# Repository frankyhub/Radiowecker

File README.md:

<div align="center">

|[:skull:ISSUE](https://github.com/frankyhub/Radiowecker/issues?q=is%3Aissue)|[:speech_balloon: Forum /Discussion](https://github.com/frankyhub/Radiowecker/discussions)|[:grey_question:WiKi](https://github.com/frankyhub/Radiowecker/wiki)||
|--|--|--|--|
| | | | |
<a href="https://github.com/frankyhub/Radiowecker/issues">|<a href="https://github.com/frankyhub/Radiowecker/discussions">|<a href="https://github.com/frankyhub/Radiowecker/6eleases">||
|| <a href="https://github.com/frankyhub/Radiowecker/pulse" alt="Activity">| <a href="https://github.com/frankyhub/Radiowecker/graphs/traffic">  |<a href="https://github.com/frankyhub?tab=stars"> ||

<br>
  
<br> <br>

</div>

## Story
Das Repo beschreibt einen Radiowecker mit einem 2,8"T FT-Display, einem 3W Klasse D Amplifier und einen WEB-Server. Zwei Weckzeiten können an beliebigen Wochentagen zugeordnet werden. Es ist auch ein Einschlaf-Timer vorhanden. Mit dem LDR kann man die Display-Helligkeit automatisch an die Raumhelligkeit anpassen. Über den Touchscreen sind Radio ein/aus, Einschlaftimer mit Einschlafzeit, Wecker ein/aus, Senderauswahl und Lautstärke einstellbar. Die Weckzeiten und die Stream-URLs der Radiostationen werden über ein Web-Interface konfiguriert.

Nach einer Idee und Vorlage von 

https://www.az-delivery.de/blogs/azdelivery-blog-fur-arduino-und-raspberry-pi/internet-radiowecker-mit-touchscreen.

## Inbetriebnahme

### Verdrahtung 

| TFT-Display | ESP32 | 
| -------- | -------- | 
|  VCC  |  3,3V  |
|  GND |   GDN |
| CS  | GPIO5  |
| RESET  | GPIO22   |
| DC | NC  |
| SDI  | GPIO23    |
| SCK  |  GPIO18  |
|  LED |  GPIO15  |
|  MISO | GPIO19   | 
| T-CLK  | GPIO18 |    
| T-CS  | GPIO14  | 
| T-DIN  | GPIO23  | 
| T-DO  | GPIO19  | 
| T-IRQ  | GPIO27  | 
|  --- |  --- | 

<br> <br>

### ESP32 TFT 2.8" Shield

<br> <br>

### Gehäuse

<br> <br>

### Nach anlegen der Versorgungsspannung startet der Accesspoit. In den Einstellungen des Handys oder Tablets wird das WLAN "Radiowecker" ausgewählt 

<br> <br>

<br> <br>

### und über einen Browser die URL 192.168.4.1 eingegeben und der Neustart-Button betätigt.

<br> <br>

### Am Seriellen Monitor kann der Startvorgang beobachtet und die IP-Adresse des WEB-Servers abgelesen werden.

<br> <br>

### Am Display wird beim Startvorgang die WLAN-Verbindung angezeigt.

<br> <br>

### Nach dem Aufruf des WEB-Server sieht man die Einstellungen und passt diese an.

<br> <br>

### Die Bedienung kann auch über das TFT-Display erfolgen.

<br> <br>

<br> <br>

## Bedienung

### Radio ein/aus
Das Radio wird ein- oder ausgeschaltet. Die Anzeige kehrt zur Zeitanzeige zurück. Wurde das Radio eingeschaltet, erscheint unter der Zeitanzeige der Radioblock mit dem Sendernamen.

### Einschlaftimer
Die Einschlafzeit wird gestartet. Falls das Radio nicht eingeschaltet ist, wird es eingeschaltet. Die Anzeige kehrt zur Zeitanzeige zurück. Wenn die eingestellte Einschlafzeit vorüber ist, wird das Radio automatisch ausgeschaltet.

### Wecker ein/aus
Die Wecker-Funktion wird ein- oder ausgeschaltet. Die Anzeige kehrt zur Zeitanzeige zurück. Wurde der Wecker eingeschaltet, erscheint ganz unten im Display der Wochentag und die Uhrzeit, wann der Wecker das nächste Mal ausgelöst wird. Wenn der angezeigte Wochentag und die Uhrzeit zutreffen, wird das Radio automatisch eingeschaltet.

### Sender speichern
Der ausgewählte Sender wird als aktiver Sender übernommen. Ist das Radio gerade eingeschaltet, so wechselt der Stream automatisch auf den neuen Sender. Die Anzeige kehrt zur Zeitanzeige zurück.

### Zurück
Die Anzeige kehrt zur Zeitanzeige zurück.

Erfolgt 10 Sekunden keine Aktivität, so kehrt die Anzeige automatisch zur Zeitanzeige zurück. Alle Einstellungsänderungen werden in den Präferenzen gespeichert. Die Bedienungsseite wird immer mit voller Helligkeit dargestellt.

<br> <br>

## Konfiguration

### Über die URL http://radiowecker/ sollte die Konfigurationsseite abrufbar sein. 

<br> <br>

Im oberen Teil sieht man die WLAN-Zugangsdaten und den NTP-Server. Mit dem "Speichern-Button" werden Änderungen wirksam. Auch ein Neustart ist möglich. Als Nächstes folgen die Weckzeiten. Zwei Weckzeiten sind möglich. Für jede der Weckzeiten sind die Wochentage wählbar, an denen die Weckzeiten anzuwenden sind. Die Dropdown-Liste darunter enthält alle Sender der Senderliste. Auswählbare Sender haben vor dem Namen einen schwarzen Punkt. Im Formular darunter werden die Daten zur ausgewählten Station angezeigt und können geändert werden. Ist das Häkchen bei „Verwenden“ nicht gesetzt, ist die Station im Gerät nicht aktiv. Da manche URLs nicht funktionieren, sollte man eine neue URL erstmal testen. Ein Klicken auf den "Testen-Button" startet die Wiedergabe der URL am eingeschalteten Gerät. Sollte die Wiedergabe nicht funktionieren, wird wieder auf den aktuellen Sender zurückgeschaltet und eine Meldung angezeigt. Ist die Wiedergabe möglich, wird eine Box mit einem Knopf angezeigt. Klicken auf diesen Knopf schließt die Box und beendet den Test. Es wird wieder die aktuelle Station wiedergegeben. Im Eingabefeld „Position“ wird die Position der ausgewählten Station innerhalb der Senderliste angezeigt. Durch eine Änderung dieses Wertes, kann die Station auf die angegebene Position verschoben und mit dem Knopf „Ändern“ können die Änderungen für die ausgewählte Station dauerhaft geändert werden.

---

<br> <br>

---

<div style="position:absolute; left:2cm; "> <ol class="breadcrumb" style="border-top: 2px solid black;border-bottom:2px solid black; height: 45px; width: 900px;"> <p align="center"><a href="#oben">nach oben</a></p></ol>
</div>  

---

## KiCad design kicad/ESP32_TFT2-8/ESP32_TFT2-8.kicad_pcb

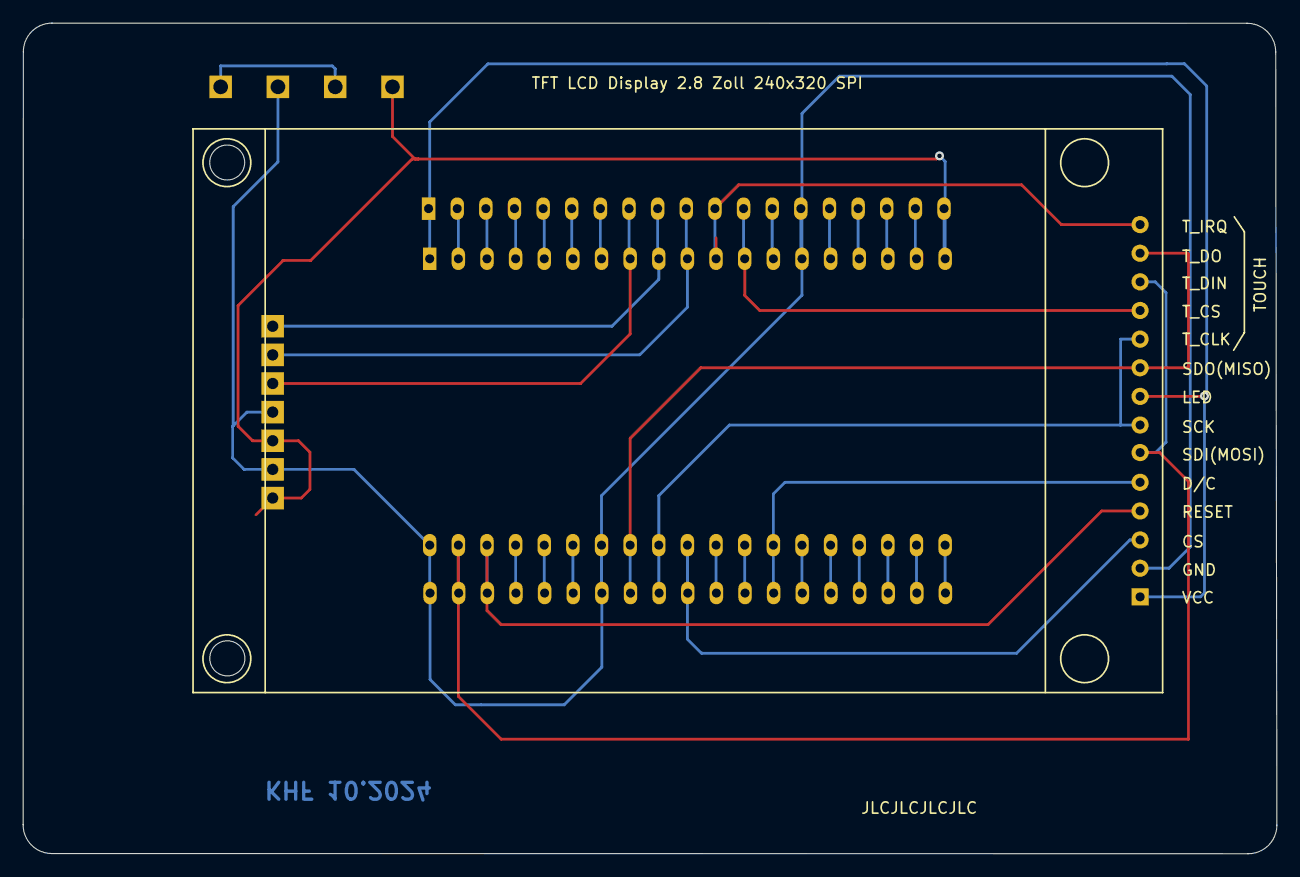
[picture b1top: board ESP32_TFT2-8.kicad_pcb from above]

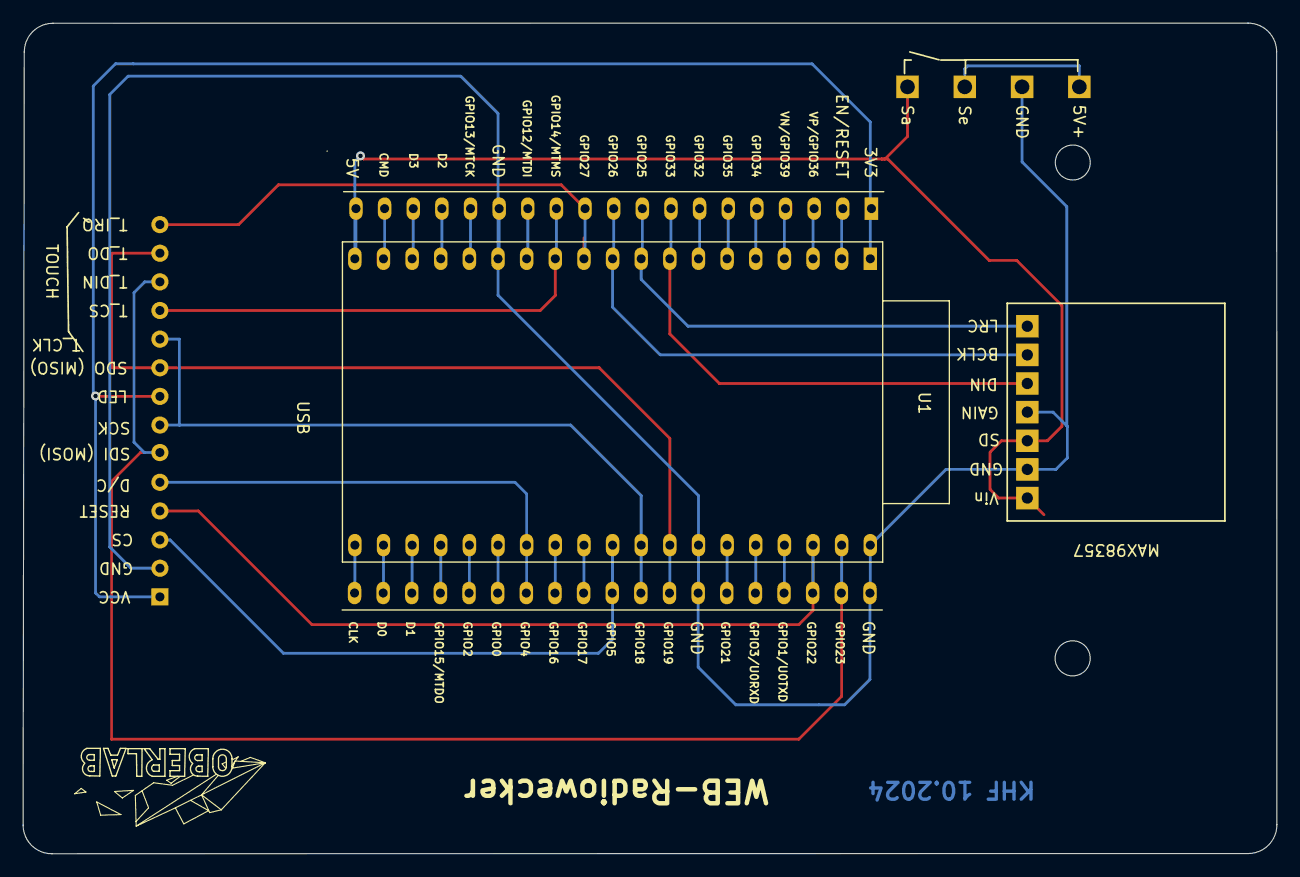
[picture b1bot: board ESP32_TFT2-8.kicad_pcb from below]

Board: 2 copper layers, 111.2 x 73.7 mm, 13 parts (8 on the bottom side), 14 nets.

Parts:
U1: ESP32-DevKitC
U2: 2.8_tft_240x320_touch_sd_spi
U3: 5V+; LP
U4, U8: GND; LP
U5: Se; LP
U6: Sa; LP
U7: Vin; LP
U9: SD; LP
U10: GAIN; LP
U11: DIN; LP
U12: BCLK; LP
U13: LRC; LP

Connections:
unnamed: U1.1 (3V3), U2.1 (VCC), U2.8 (LED)
unnamed: U1.19 (5V), U6.1 (LP), U7.1 (LP), U9.1 (LP)
unnamed: U1.8 (32K_XN/GPIO33/ADC1_CH5), U11.1 (LP)
unnamed: U1.11 (ADC2_CH7/GPIO27), U2.14 (T_IRQ)
unnamed: U1.9 (DAC_1/ADC2_CH8/GPIO25), U13.1 (LP)
unnamed: U1.10 (DAC_2/ADC2_CH9/GPIO26), U12.1 (LP)
unnamed: U1.29 (GPIO5), U2.3 (CS)
unnamed: U1.30 (GPIO18), U2.7 (SCK), U2.10 (T_CLK)
unnamed: U1.31 (GPIO19), U2.9 (MISO), U2.13 (T_DQ)
unnamed: U1.36 (GPIO22), U2.4 (RESET)
unnamed: U1.37 (GPIO23), U2.6 (MOSI), U2.12 (T_DIN)
unnamed: U1.12 (MTMS/GPIO14/ADC2_CH6), U2.11 (T_CS)
unnamed: U3.1 (LP), U5.1 (LP)
unnamed: U1.14 (GND), U1.32 (GND), U1.38 (GND), U2.2 (GND), U4.1 (LP), U8.1 (LP), U10.1 (LP)

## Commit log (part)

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2024-07-08 V 08072024
2024-07-09 V 07072024
2024-07-09 V 09.07.2024
2024-07-09 V 09072024
2024-07-10 V10072024
2024-07-10 V 10072024
2024-07-13 V 13072024
2024-07-13 V 13072023
2024-08-30 v1.2.1
2024-09-10 V 10092024
2024-10-02 V 02102024
2024-10-03 V 03102024
2024-10-12 V12102024
